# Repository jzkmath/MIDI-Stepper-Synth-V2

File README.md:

# MIDI-Stepper-Synth-V2
This is the Version 2 of my MIDI Stepper Synth. The key differences between this and Version 1 is
that this version uses the Terasic DE0-nano (Cyclone IV) FPGA as the controller instead of Arduino.
The key advantage to doing so is that an FPGA can execute commands at the same time instead of sequentially.
This also allows for a better understanding of how MIDI actually works, because the MIDI has to be decoded manually
instead of using a MIDI library.

This project is being performed at the Virginia Tech AMP Lab, and the project can be seen (Link is dead)

Alternatively, you can view the project documentation/Notes in the "Project Documentation" folder and opening the "Documentation.md" file.

**Please use the project page or PDF to see the BOM and all information on this project!!!**

Since MIDI uses a specific type of UART, the FPGA will take the serial data and convert it to parallel, as a 3 byte register.
Once this is done, the message is decoded such that the stepper motors react accordingly. 

## Basic MIDI Layout
The 3 byte MIDI Message is as Follows:
**1XXXCCCC 0NNNNNNN 0VVVVVVV**
- **X** - MIDI Command. This is 1000 for Note OFF, and 1001 for Note ON.
- **C** - MIDI Channel. 
- **N** - MIDI Note. This is the pitch that is specified. 60 for example is Middle C or C4.
- **V** - MIDI Velocity. This is similar to volume.

The general idea is that we want to turn the MIDI value into a stepper speed. To do this, we use a
similar method to how version 1 handles this, except this time we use clock cycles instead of time.
The DE0-nano has a 50 MHz clock, so we can generate a square wave at a specific frequency by counting
a certain number of clock cycles and toggling the state of a pin. 
The code simply takes the MIDI note value and converts it to the corresponding number of clock cycles
needed to do so.

In addition to the functions of version 1, version 2 also uses the velocity information to control 
how many steppers turn. The higher the velocity, the more stepper motors turn on (ranging from 0-4)
This is how the array of floppy drives work on the popular "Floppotron" on YouTube.

## Block Diagram

## Principle of Operation

The first thing that must be done to convert MIDI into stepper music is that we need to decode the MIDI signal. MIDI uses 31250 baud UART (Universal Asynchronous Recieve Transmit) to send an recieve data. This is a form of serial, so we need to load this into a register to act upon with combinational logic. To do this, we use a Finite State Machine, or FSM with two states; Idle and Read. 
In the Idle state, the Rx line is high. When a device wants to send a message, the Rx line is dropped low. This is known as the start bit and the actual data is the 8 bits that follow, then the line goes high again (called the stop bit).

Knowing this, we can use the start bit as a means to change to the read state. 

In the read state, we want to look at the Rx line in the middle of each bit and shift that bit into our register. To do this, we count a certain number of clock cycles to get to the center of the bit. Given that the DE0-nano has a 50MHz clock and MIDI is 31250 baud, that means that it takes 800 clock cycles to get to the center of a bit, and 1600 clock cycles to go from center to center.

When the start bit is detected the read process is as follows:
1. count 800 clock cycles to get to the center of the start bit
2. count 1600 clock cycles to get to the center of the data bit
3. shift in the value of the Rx line
4. repeat steps 2 and 3 a total of 8 times
5. output the shifted value
6. wait for the Rx line to go high (stop bit detected) and go back to the Idle state.

Once we do that, we have our byte of data. Knowing that MIDI is 3 bytes of data, we take the byte and shift it into a larger, 3 byte register. After that, we can use combinational logic to control the stepper motors.

MIDI has a byte of control information (Command and Channel) and two bytes of data (Pitch and Velocity). We want to use the first byte to properly route the last two bytes appropriately. To do this, we have a single data router module and register modules for each channel. The registers have an enable and clear control signal and will either load or clear their contents depending on which input is pulled high. The second and third bytes are connected to the inputs of all the registers via a common bus and the first byte is used by the router module to control which register gets enable or clear pulled high. Note on (1001) or Note Off (1000) determines whether the register is enabled or cleared, and the channel determines which channel this happens to.

Once the register has the data, we need to convert the pitch into clock cycles. We look at the pitch value and corresponding frequency. We then figure out how many clock cycles elapse in half the period of the note. We do half because we want to create a square wave, which has a 50% duty cycle.

Using the converted value, we have a module count up to that value and then toggle the state of the pin. This is the equivalent to the "Blink without delay" sketch that is used in Arduinos (except for FPGAs).

Finally, we use the velocity value to determine how many stepper motors get that signal, which can be anywhere between 0 and 4.

## Credits
The basic UART decoding Verilog code is based off code provided by Electronoobs, modified to be more stable and work with MIDI.

Special Thanks to Robert Perkel and Bob Lineberry for helping with this project and providing assistance with this.

## Legal
This project is under the GNU GPL3.0 Open Source License. 
You are free to use the code in your project, so long as you credit the creator (Jonathan Kayne).
I want people to be able to use my code, but I don't want people to plagiarize my work!

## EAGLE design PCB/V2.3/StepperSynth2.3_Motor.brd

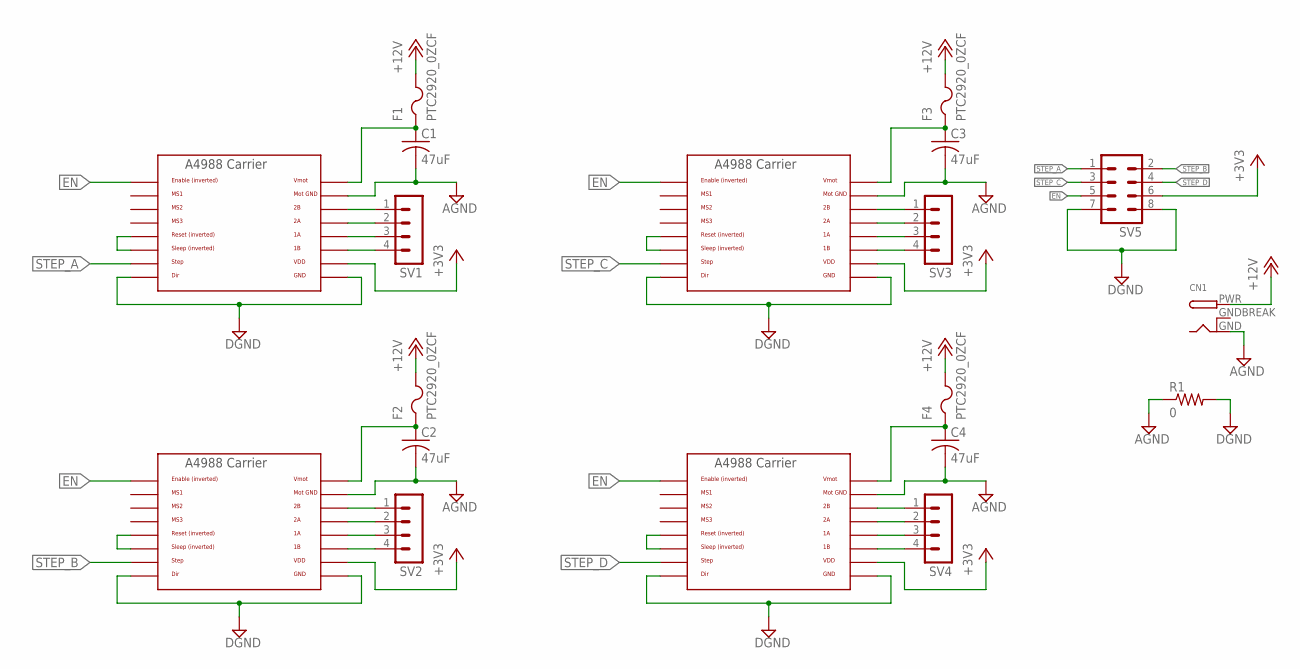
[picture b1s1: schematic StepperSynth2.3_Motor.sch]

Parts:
C1, C2, C3, C4: 47uF; E5-10
CN1: DCBARRELPTH; DCJACK_2MM_PTH
F1, F2, F3, F4: PTC2920_0ZCF; 0ZCF
R1: 0; 0204/5
SV1, SV2, SV3, SV4: MA04-1
SV5: MA04-2
U$1, U$2, U$3, U$4: A4988BREAKOUT

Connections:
+3V3: SV5.6, U$1.VDD, U$2.VDD, U$3.VDD, U$4.VDD
+12V: CN1.PWR, F1.2, F2.2, F3.2, F4.2
AGND: C1.-, C2.-, C3.-, C4.-, CN1.GND, R1.1, U$1.MOTGND, U$2.MOTGND, U$3.MOTGND, U$4.MOTGND
DGND: R1.2, SV5.7, SV5.8, U$1.DIR, U$1.GND, U$2.DIR, U$2.GND, U$3.DIR, U$3.GND, U$4.DIR, U$4.GND
EN: SV5.5, U$1.EN, U$2.EN, U$3.EN, U$4.EN
GNDBREAK: CN1.GNDBREAK
unnamed: SV1.1, U$1.2B
unnamed: SV1.2, U$1.2A
unnamed: SV1.3, U$1.1A
unnamed: SV1.4, U$1.1B
unnamed: U$1.RST, U$1.SLP (SLEEP)
unnamed: C1.+, F1.1, U$1.VMOT
unnamed: SV2.1, U$2.2B
unnamed: SV2.2, U$2.2A
unnamed: SV2.3, U$2.1A
unnamed: SV2.4, U$2.1B
unnamed: U$2.RST, U$2.SLP (SLEEP)
unnamed: C2.+, F2.1, U$2.VMOT
unnamed: SV3.1, U$3.2B
unnamed: SV3.2, U$3.2A
unnamed: SV3.3, U$3.1A
unnamed: SV3.4, U$3.1B
unnamed: U$3.RST, U$3.SLP (SLEEP)
unnamed: C3.+, F3.1, U$3.VMOT
unnamed: SV4.1, U$4.2B
unnamed: SV4.2, U$4.2A
unnamed: SV4.3, U$4.1A
unnamed: SV4.4, U$4.1B
unnamed: U$4.RST, U$4.SLP (SLEEP)
unnamed: C4.+, F4.1, U$4.VMOT
STEP_A: SV5.1, U$1.STEP
STEP_B: SV5.2, U$2.STEP
STEP_C: SV5.3, U$3.STEP
STEP_D: SV5.4, U$4.STEP

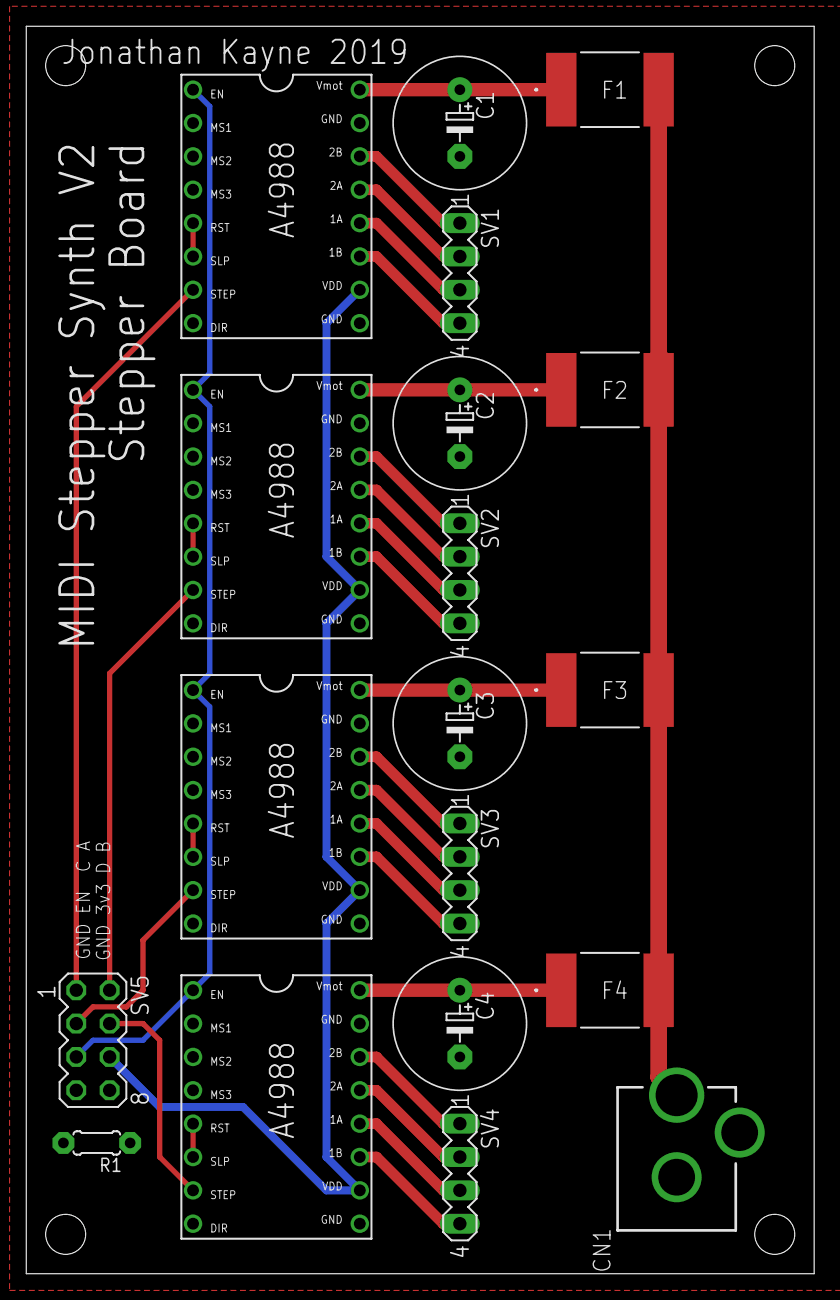
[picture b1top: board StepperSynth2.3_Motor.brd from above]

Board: 2 copper layers, 60.0 x 95.0 mm, 19 parts (0 on the bottom side), 33 nets.

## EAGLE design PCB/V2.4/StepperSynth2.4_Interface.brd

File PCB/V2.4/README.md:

### Stepper Synth V2.4

This is the Final Revision of the MIDI Stepper Synth V2 PCBs. They were designed in Eagle, and rendered in KiCAD.

I added new connectors and changed the header sockets to be in a zigzag pattern so that they would be easier to solder.

## Interface PCB

## Motor PCB

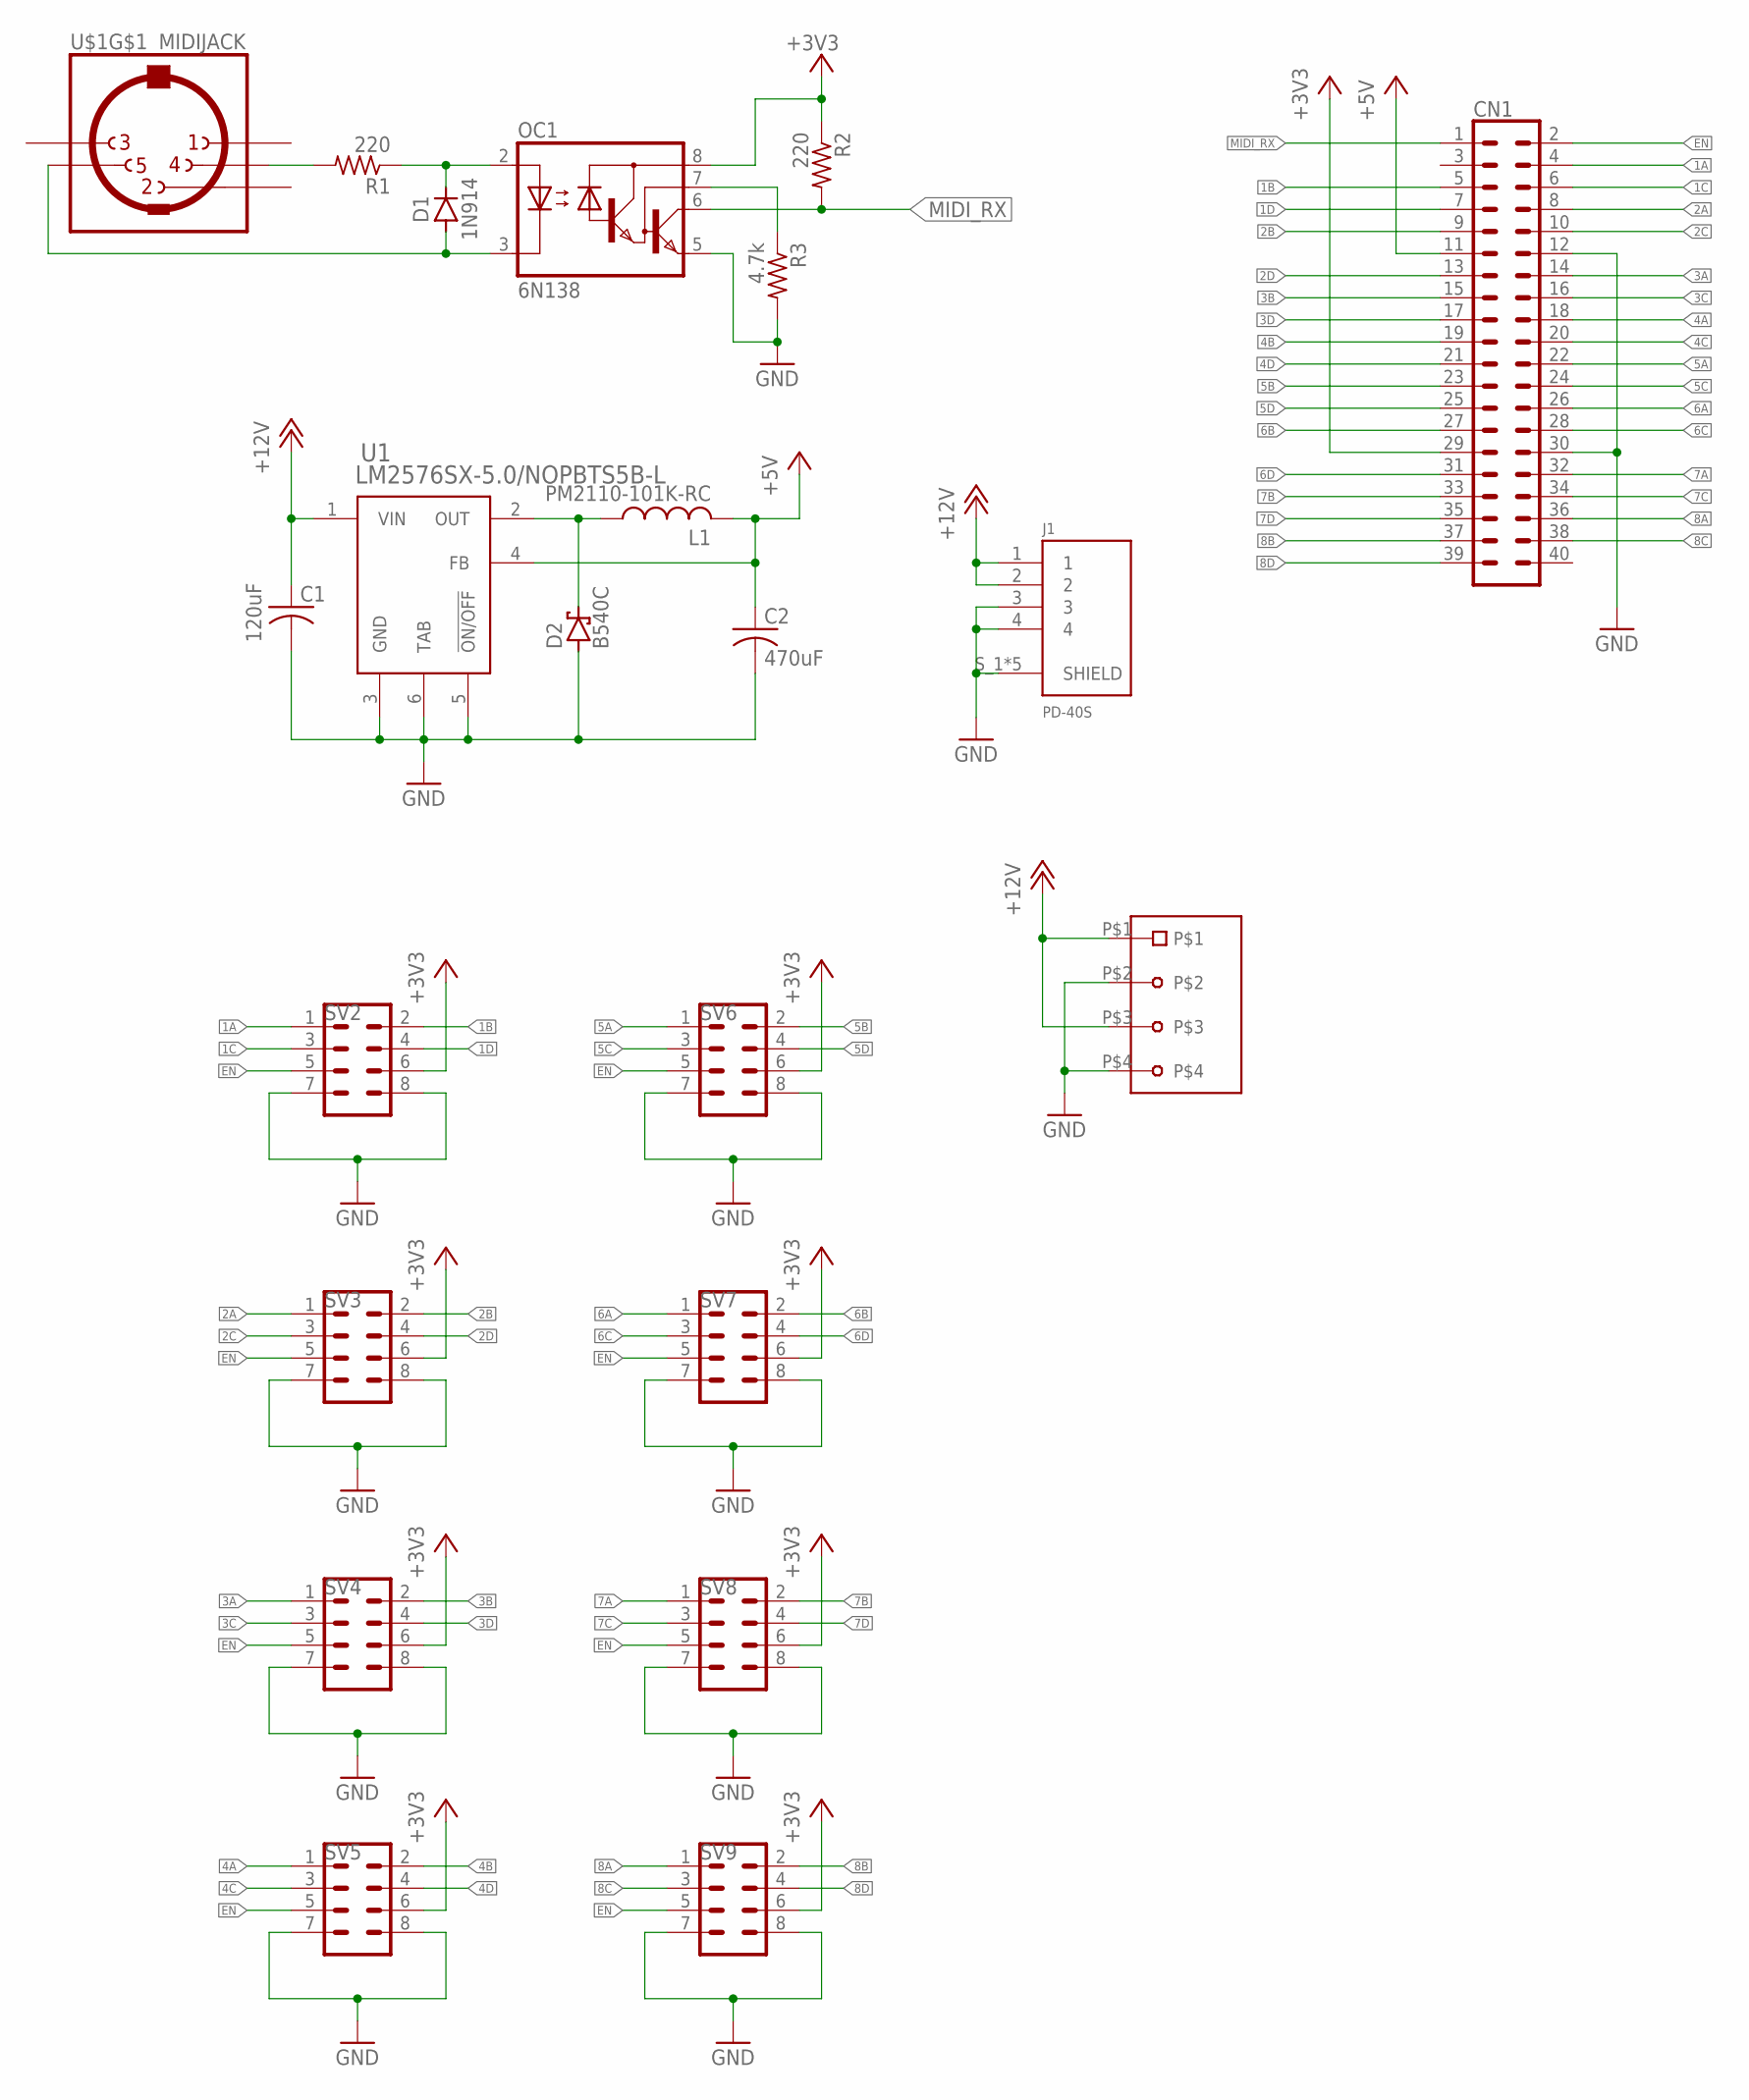
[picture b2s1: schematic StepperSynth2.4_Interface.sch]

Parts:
C1: 120uF; PCAP_SVP_C6-L
C2: 470uF; U2-P-L
CN1: CONN_20X2_LOCK; 1X20_LOCK
CN2: SCREW_TERMINAL_4POS_5MM; 4_POS-SCREW_TERM
D1: 1N914; DO35-7
D2: B540C; SMC
J1: PD-40S; CUI_PD-40S
L1: PM2110-101K-RC; IND_PM2110
OC1: 6N138; DIL08
R1, R2: 220; 0204/7
R3: 4.7k; 0204/7
SV2, SV3, SV4, SV5, SV6, SV7, SV8, SV9: CONN_4X2_LOCK; 1X04_LOCK
U1: LM2576SX-5.0/NOPBTS5B-L; TS5B-L
U$1: MIDIJACK; CP-2350

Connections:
1A: CN1.4, SV2.1
1B: CN1.5, SV2.2
1C: CN1.6, SV2.3
1D: CN1.7, SV2.4
2A: CN1.8, SV3.1
2B: CN1.9, SV3.2
2C: CN1.10, SV3.3
2D: CN1.13, SV3.4
3A: CN1.14, SV4.1
3B: CN1.15, SV4.2
3C: CN1.16, SV4.3
3D: CN1.17, SV4.4
4A: CN1.18, SV5.1
4B: CN1.19, SV5.2
4C: CN1.20, SV5.3
4D: CN1.21, SV5.4
5A: CN1.22, SV6.1
5B: CN1.23, SV6.2
5C: CN1.24, SV6.3
5D: CN1.25, SV6.4
6A: CN1.26, SV7.1
6B: CN1.27, SV7.2
6C: CN1.28, SV7.3
6D: CN1.31, SV7.4
7A: CN1.32, SV8.1
7B: CN1.33, SV8.2
7C: CN1.34, SV8.3
7D: CN1.35, SV8.4
8A: CN1.36, SV9.1
8B: CN1.37, SV9.2
8C: CN1.38, SV9.3
8D: CN1.39, SV9.4
+3V3: CN1.29, OC1.8 (VCC), R2.1, SV2.6, SV3.6, SV4.6, SV5.6, SV6.6, SV7.6, SV8.6, SV9.6
+5V: C2.1 (+), CN1.11, L1.2, U1.4 (FB)
+12V: C1.1 (+), CN2.P$1, CN2.P$3, J1.1, J1.2, U1.1 (VIN)
EN: CN1.2, SV2.5, SV3.5, SV4.5, SV5.5, SV6.5, SV7.5, SV8.5, SV9.5
GND: C1.2 (-), C2.2 (-), CN1.12, CN1.30, CN2.P$2, CN2.P$4, D2.A, J1.3, J1.4, J1.S_1 (SHIELD), J1.S_2 (SHIELD), J1.S_3 (SHIELD), J1.S_4 (SHIELD), J1.S_5 (SHIELD), OC1.5 (GND), R3.2, SV2.7, SV2.8, SV3.7, SV3.8, SV4.7, SV4.8, SV5.7, SV5.8, SV6.7, SV6.8, SV7.7, SV7.8, SV8.7, SV8.8, SV9.7, SV9.8, U1.3 (GND), U1.5 (!ON/OFF), U1.6 (TAB)
MIDI_RX: CN1.1, OC1.6 (VO), R2.2
unnamed: R1.2, U$1.4
unnamed: D1.C, OC1.2 (A), R1.1
unnamed: D1.A, OC1.3 (C), U$1.5
unnamed: OC1.7 (VB), R3.1
unnamed: D2.C, L1.1, U1.2 (OUT)

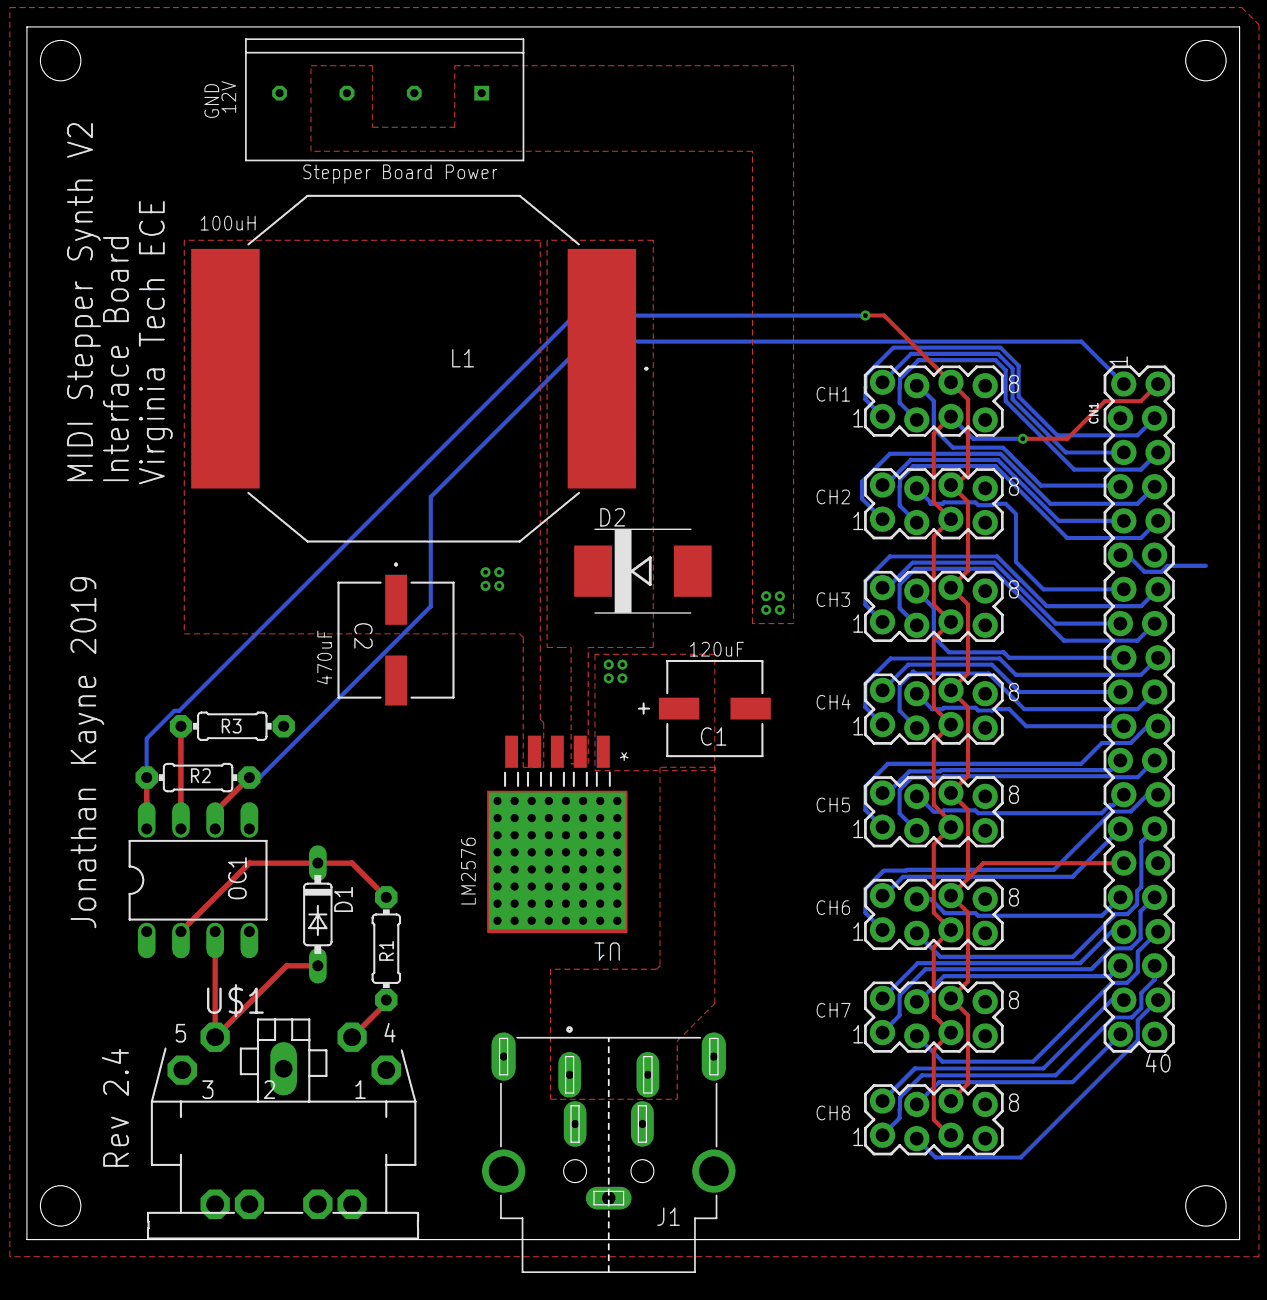
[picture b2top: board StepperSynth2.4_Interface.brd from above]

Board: 2 copper layers, 89.9 x 92.4 mm, 22 parts (0 on the bottom side), 43 nets.

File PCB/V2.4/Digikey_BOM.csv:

"Manufacturer Part Number","Manufacturer","Digi-Key Part Number","Customer Reference","Reference Designator","Packaging","Part Status","Quantity","Unit Price","Extended Price","Quantity Available","Mfg Std Lead Time","Description","RoHS Status","Lead Free Status","REACH Status","US Tariff Status"
"VES120PS12","XP Power","1470-3639-ND","","","Box","Active","1","62.00000","$62.00","498","21 Weeks","EXTERNAL PSU, 120W, LEVEL VI","RoHS Compliant","Lead free","Not Available","Tariff Eligible"
"PD-40S","CUI Inc.","CP-7240-ND","","","Tray","Active","1","2.59000","$2.59","12445","14 Weeks","CONN JACK FMALE DIN 4POS SOLDER","RoHS Compliant","Lead free","Not Available","Tariff Eligible"
"OSTTA020161","On Shore Technology Inc.","ED2561-ND","","","Bulk","Active","8","0.69000","$5.52","16887","12 Weeks","TERM BLK 2POS SIDE ENTRY 5MM PCB","RoHS Compliant","Lead free","REACH Unaffected","Tariff Applied"
"OSTTA040161","On Shore Technology Inc.","ED2563-ND","","","Bulk","Active","1","1.05000","$1.05","976","12 Weeks","TERM BLK 4POS SIDE ENTRY 5MM PCB","RoHS Compliant","Lead free","REACH Unaffected","Tariff Applied"
"61300411121","Wurth Electronics Inc.","732-5317-ND","","","Bag","Active","32","0.12720","$4.07","16252","14 Weeks","CONN HEADER VERT 4POS 2.54MM","RoHS Compliant","Lead free","REACH Unaffected",""
"PPTC081LFBN-RC","Sullins Connector Solutions","S7006-ND","","","Tray","Active","64","0.60800","$38.91","21240","5 Weeks","CONN HDR 8POS 0.1 TIN PCB","RoHS Compliant","Lead free","REACH Unaffected",""
"0ZCF0100AF2A","Bel Fuse Inc.","507-2070-1-ND","","","Cut Tape (CT)","Active","32","0.49100","$15.71","9184","18 Weeks","PTC RESET FUSE 60V 1A 2920","RoHS Compliant","Lead free","REACH Unaffected",""
"UHE2A470MPD1TD","Nichicon","493-14555-1-ND","","","Cut Tape (CT)","Active","36","0.36000","$12.96","50826","16 Weeks","CAP ALUM 47UF 20% 100V RADIAL","RoHS Compliant","Lead free","REACH Unaffected",""
"M20-9760442","Harwin Inc.","952-3276-ND","","","Bulk","Active","16","0.31900","$5.10","3637","10 Weeks","CONN HEADER VERT 8POS 2.54MM","RoHS Compliant","Lead free","REACH Unaffected",""
"SDS-50J","CUI Inc.","CP-2350-ND","","","Tray","Active","1","1.96000","$1.96","24579","14 Weeks","CONN RCPT FMALE DIN 5POS SOLDER","RoHS Compliant","Lead free","Not Available","Tariff Applied"
"A 08-LC-TT","Assmann WSW Components","AE9986-ND","","","Tube","Active","1","0.18000","$0.18","100334","20 Weeks","CONN IC DIP SOCKET 8POS TIN","RoHS Compliant","Lead free","REACH Unaffected","Tariff Eligible"
"1N914","ON Semiconductor","1N914FS-ND","","","Bulk","Active","1","0.10000","$0.10","50588","17 Weeks","DIODE GEN PURP 100V 200MA DO35","RoHS Compliant","Lead free","REACH Unaffected","Tariff Applied"
"61304021121","Wurth Electronics Inc.","732-5310-ND","","","Bag","Active","1","1.89000","$1.89","924","14 Weeks","CONN HEADER VERT 40POS 2.54MM","RoHS Compliant","Lead free","REACH Unaffected",""
"20SVPF120M","Panasonic Electronic Components","P16498CT-ND","","","Cut Tape (CT)","Active","1","1.29000","$1.29","34887","9 Weeks","CAP ALUM POLY 120UF 20% 20V SMD","RoHS Compliant","Lead free","Not Available",""
"UUD1A471MNL1GS","Nichicon","493-2252-1-ND","","","Cut Tape (CT)","Active","1","0.68000","$0.68","34069","18 Weeks","CAP ALUM 470UF 20% 10V SMD","RoHS Compliant","Lead free","REACH Unaffected",""
"B540C-13-F","Diodes Incorporated","B540C-FDICT-ND","","","Cut Tape (CT)","Active","1","0.50000","$0.50","259459","13 Weeks","DIODE SCHOTTKY 40V 5A SMC","RoHS Compliant","Contains lead","REACH Unaffected",""
"PM2110-101K-RC","Bourns Inc.","M8767-ND","","","Bulk","Active","1","2.96000","$2.96","2757","20 Weeks","FIXED IND 100UH 5.4A 32 MOHM SMD","RoHS Compliant","Lead free","REACH Unaffected",""
"LM2576SX-5.0/NOPB","Texas Instruments","LM2576SX-5.0/NOPBCT-ND","","","Cut Tape (CT)","Active","1","2.86000","$2.86","41842","16 Weeks","IC REG BUCK 5V 3A TO263-5","RoHS Compliant","Contains lead","REACH Unaffected",""
"1988","Adafruit Industries LLC","1528-2235-ND","","","Bulk","Active","1","2.95000","$2.95","348","12 Weeks","GPIO RIBBON CABLE FOR RASPBERRY","Not Available","Not Available","Not Available","Tariff Eligible"
"71600-008LF","Amphenol ICC (FCI)","609-3568-ND","","","Tube","Active","16","0.87000","$13.92","6728","8 Weeks","CONN RCPT 8POS IDC 28-30AWG GOLD","RoHS Compliant","Lead free","Not Available",""
"28L0138-50R-10","Laird-Signal Integrity Products","240-2512-1-ND","","","Cut Tape (CT)","Active","10","0.07700","$0.77","44108","8 Weeks","FERRITE BEAD 153 OHM AXIAL 1LN","RoHS Compliant","Lead free","REACH Unaffected","Tariff Applied"
"CFM14JT220R","Stackpole Electronics Inc","S220QCT-ND","","","Cut Tape (CT)","Active","2","0.10000","$0.20","37986","15 Weeks","RES 220 OHM 1/4W 5% CF MINI","RoHS Compliant","Lead free","REACH Unaffected","Tariff Applied"
"CFM14JT4K70","Stackpole Electronics Inc","S4.7KQCT-ND","","","Cut Tape (CT)","Active","1","0.10000","$0.10","65820","15 Weeks","RES 4.7K OHM 1/4W 5% CF MINI","RoHS Compliant","Lead free","REACH Unaffected","Tariff Applied"
"3801/04","3M","3M156838-10-ND","","","Bulk","Active","1","3.79000","$3.79","9","Not Available","CBL RIBN 4COND 0.050 GRAY 10'","RoHS Compliant","Lead free","Not Available",""
"6N138","Lite-On Inc.","160-1795-ND","","","Tube","Active","1","0.81000","$0.81","4836","10 Weeks","OPTOISO 5KV DARL W/BASE 8DIP","RoHS Compliant","Lead free","Not Available",""

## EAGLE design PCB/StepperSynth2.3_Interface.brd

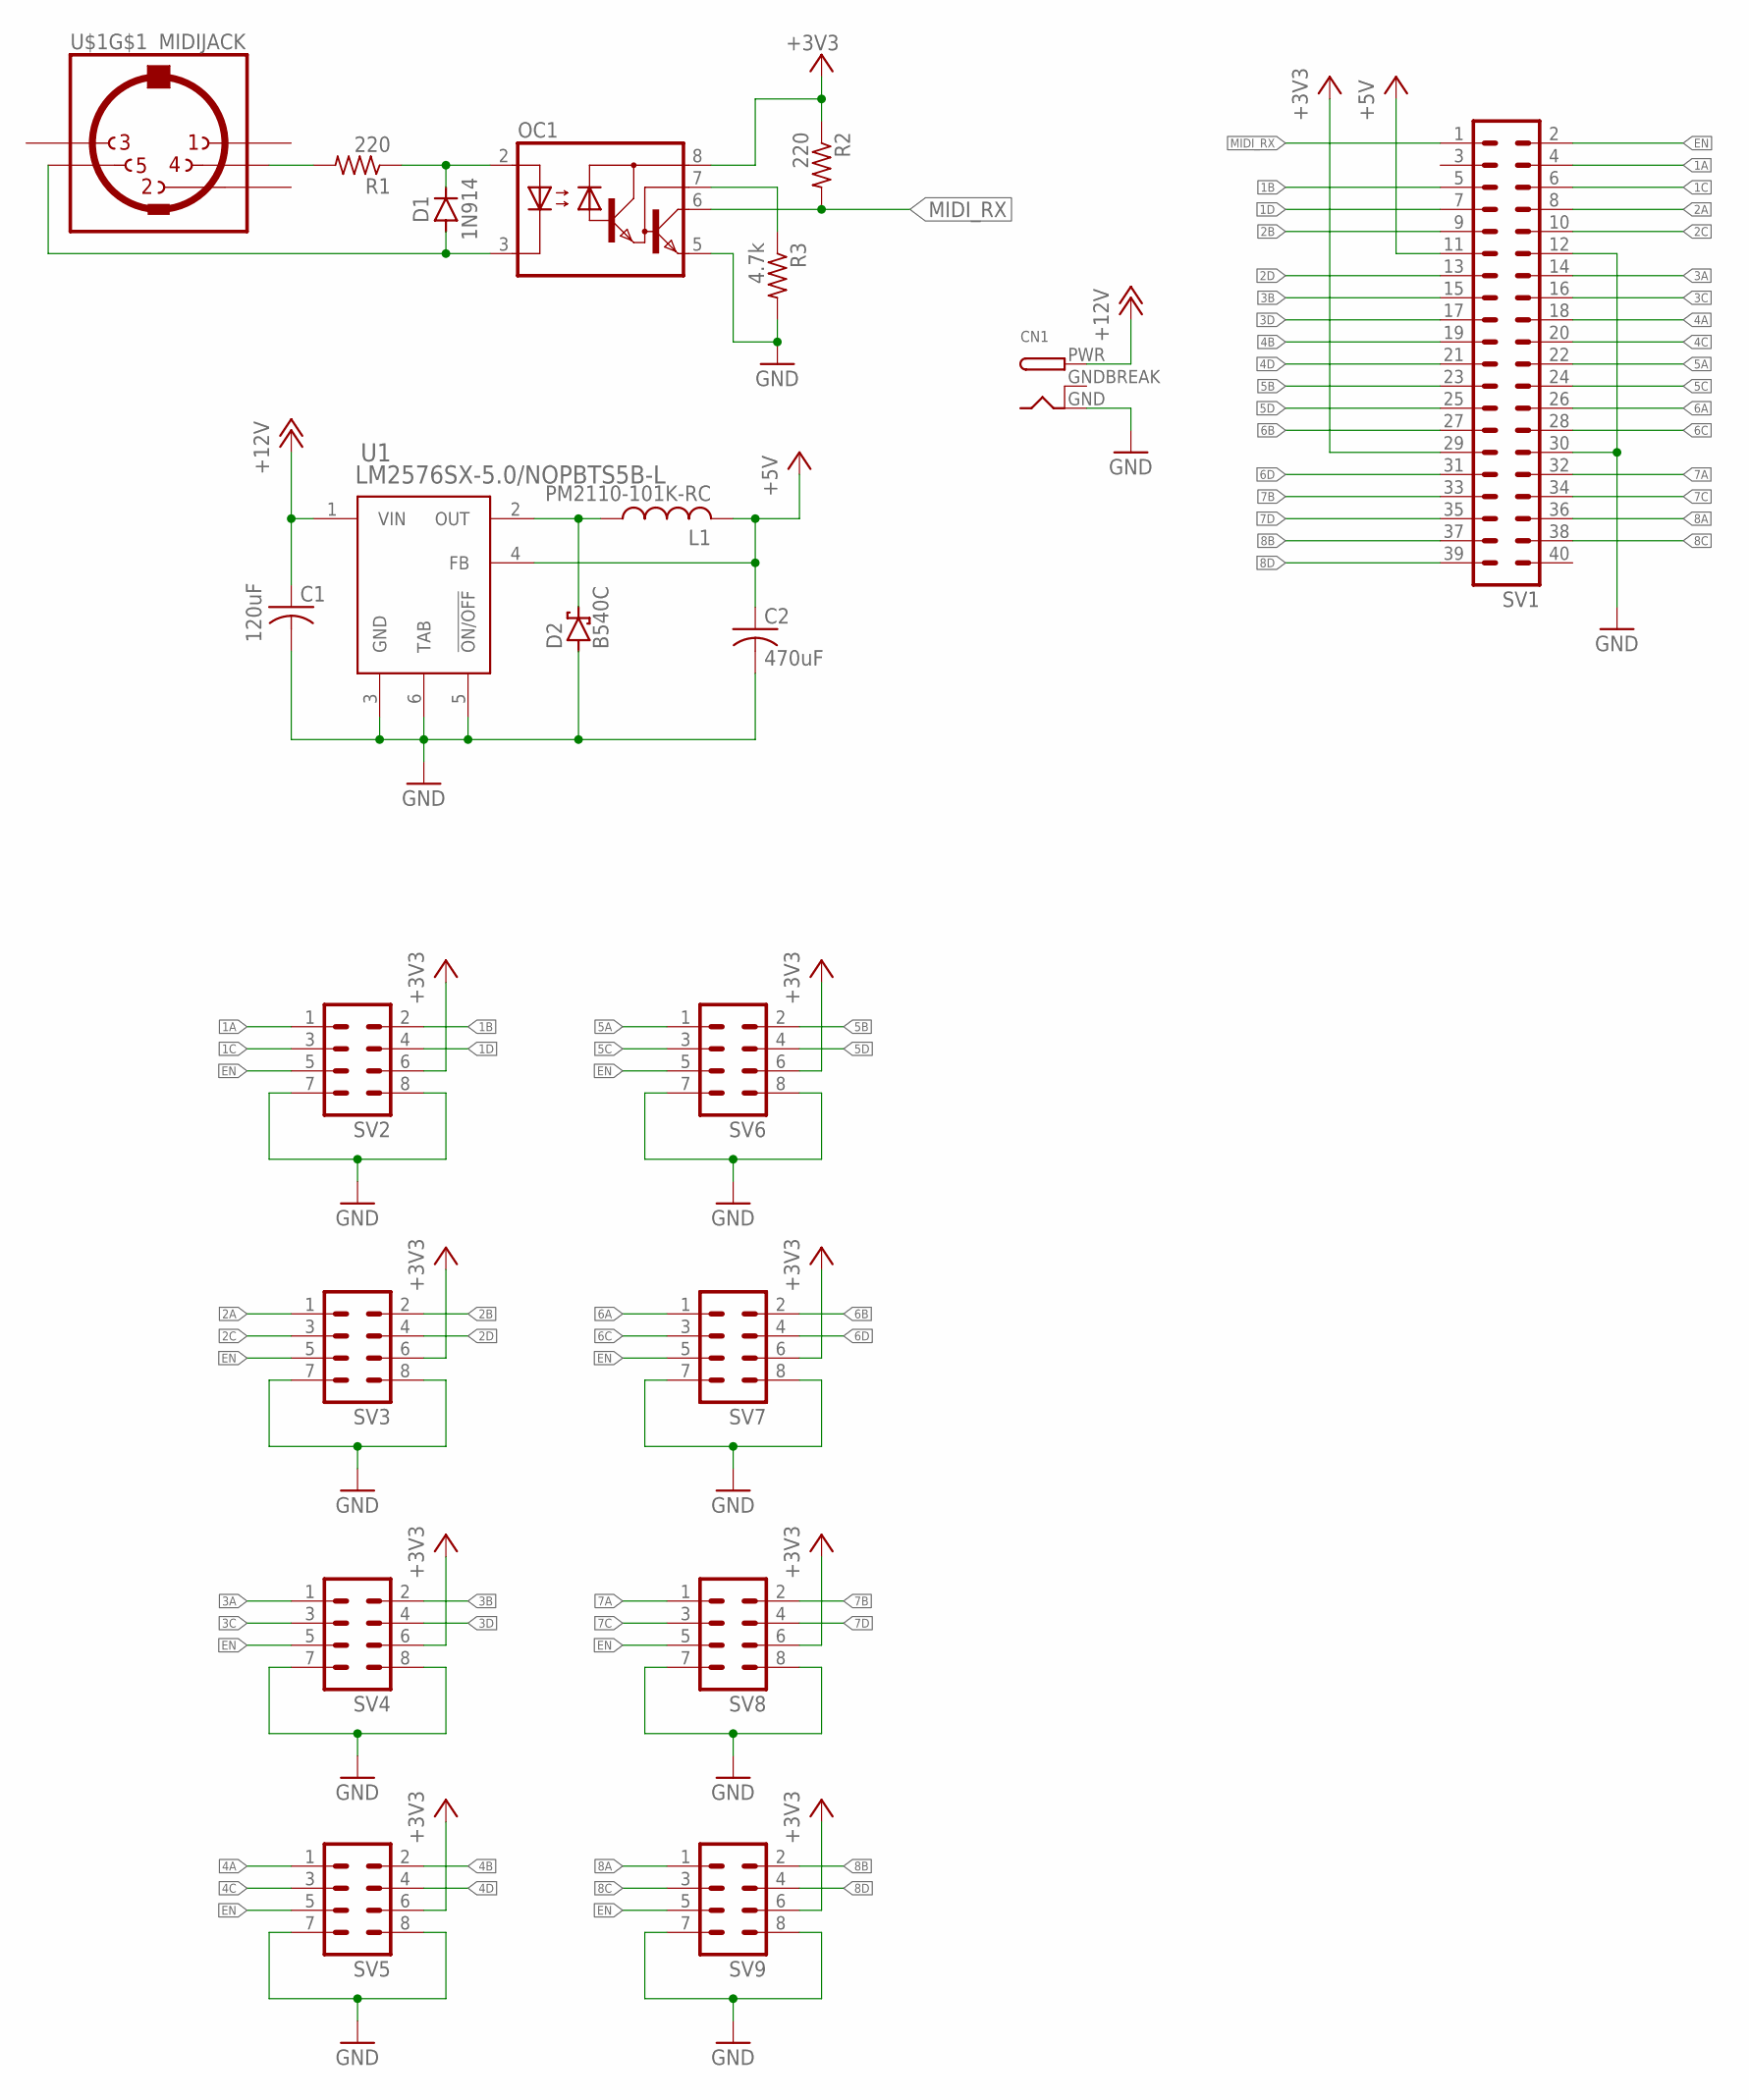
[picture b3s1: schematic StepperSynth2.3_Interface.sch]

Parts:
C1: 120uF; PCAP_SVP_C6-L
C2: 470uF; U2-P-L
CN1: DCBARRELPTH; DCJACK_2MM_PTH
D1: 1N914; DO35-7
D2: B540C; SMC
L1: PM2110-101K-RC; IND_PM2110
OC1: 6N138; DIL08
R1, R2: 220; 0204/5
R3: 4.7k; 0204/5
SV1: MA20-2
SV2, SV3, SV4, SV5, SV6, SV7, SV8, SV9: MA04-2
U1: LM2576SX-5.0/NOPBTS5B-L; TS5B-L
U$1: MIDIJACK; CP-2350

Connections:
1A: SV1.4, SV2.1
1B: SV1.5, SV2.2
1C: SV1.6, SV2.3
1D: SV1.7, SV2.4
2A: SV1.8, SV3.1
2B: SV1.9, SV3.2
2C: SV1.10, SV3.3
2D: SV1.13, SV3.4
3A: SV1.14, SV4.1
3B: SV1.15, SV4.2
3C: SV1.16, SV4.3
3D: SV1.17, SV4.4
4A: SV1.18, SV5.1
4B: SV1.19, SV5.2
4C: SV1.20, SV5.3
4D: SV1.21, SV5.4
5A: SV1.22, SV6.1
5B: SV1.23, SV6.2
5C: SV1.24, SV6.3
5D: SV1.25, SV6.4
6A: SV1.26, SV7.1
6B: SV1.27, SV7.2
6C: SV1.28, SV7.3
6D: SV1.31, SV7.4
7A: SV1.32, SV8.1
7B: SV1.33, SV8.2
7C: SV1.34, SV8.3
7D: SV1.35, SV8.4
8A: SV1.36, SV9.1
8B: SV1.37, SV9.2
8C: SV1.38, SV9.3
8D: SV1.39, SV9.4
+3V3: OC1.8 (VCC), R2.1, SV1.29, SV2.6, SV3.6, SV4.6, SV5.6, SV6.6, SV7.6, SV8.6, SV9.6
+5V: C2.1 (+), L1.2, SV1.11, U1.4 (FB)
+12V: C1.1 (+), CN1.PWR, U1.1 (VIN)
EN: SV1.2, SV2.5, SV3.5, SV4.5, SV5.5, SV6.5, SV7.5, SV8.5, SV9.5
GND: C1.2 (-), C2.2 (-), CN1.GND, D2.A, OC1.5 (GND), R3.2, SV1.12, SV1.30, SV2.7, SV2.8, SV3.7, SV3.8, SV4.7, SV4.8, SV5.7, SV5.8, SV6.7, SV6.8, SV7.7, SV7.8, SV8.7, SV8.8, SV9.7, SV9.8, U1.3 (GND), U1.5 (!ON/OFF), U1.6 (TAB)
GNDBREAK: CN1.GNDBREAK
MIDI_RX: OC1.6 (VO), R2.2, SV1.1
unnamed: R1.2, U$1.4
unnamed: D1.C, OC1.2 (A), R1.1
unnamed: D1.A, OC1.3 (C), U$1.5
unnamed: OC1.7 (VB), R3.1
unnamed: D2.C, L1.1, U1.2 (OUT)

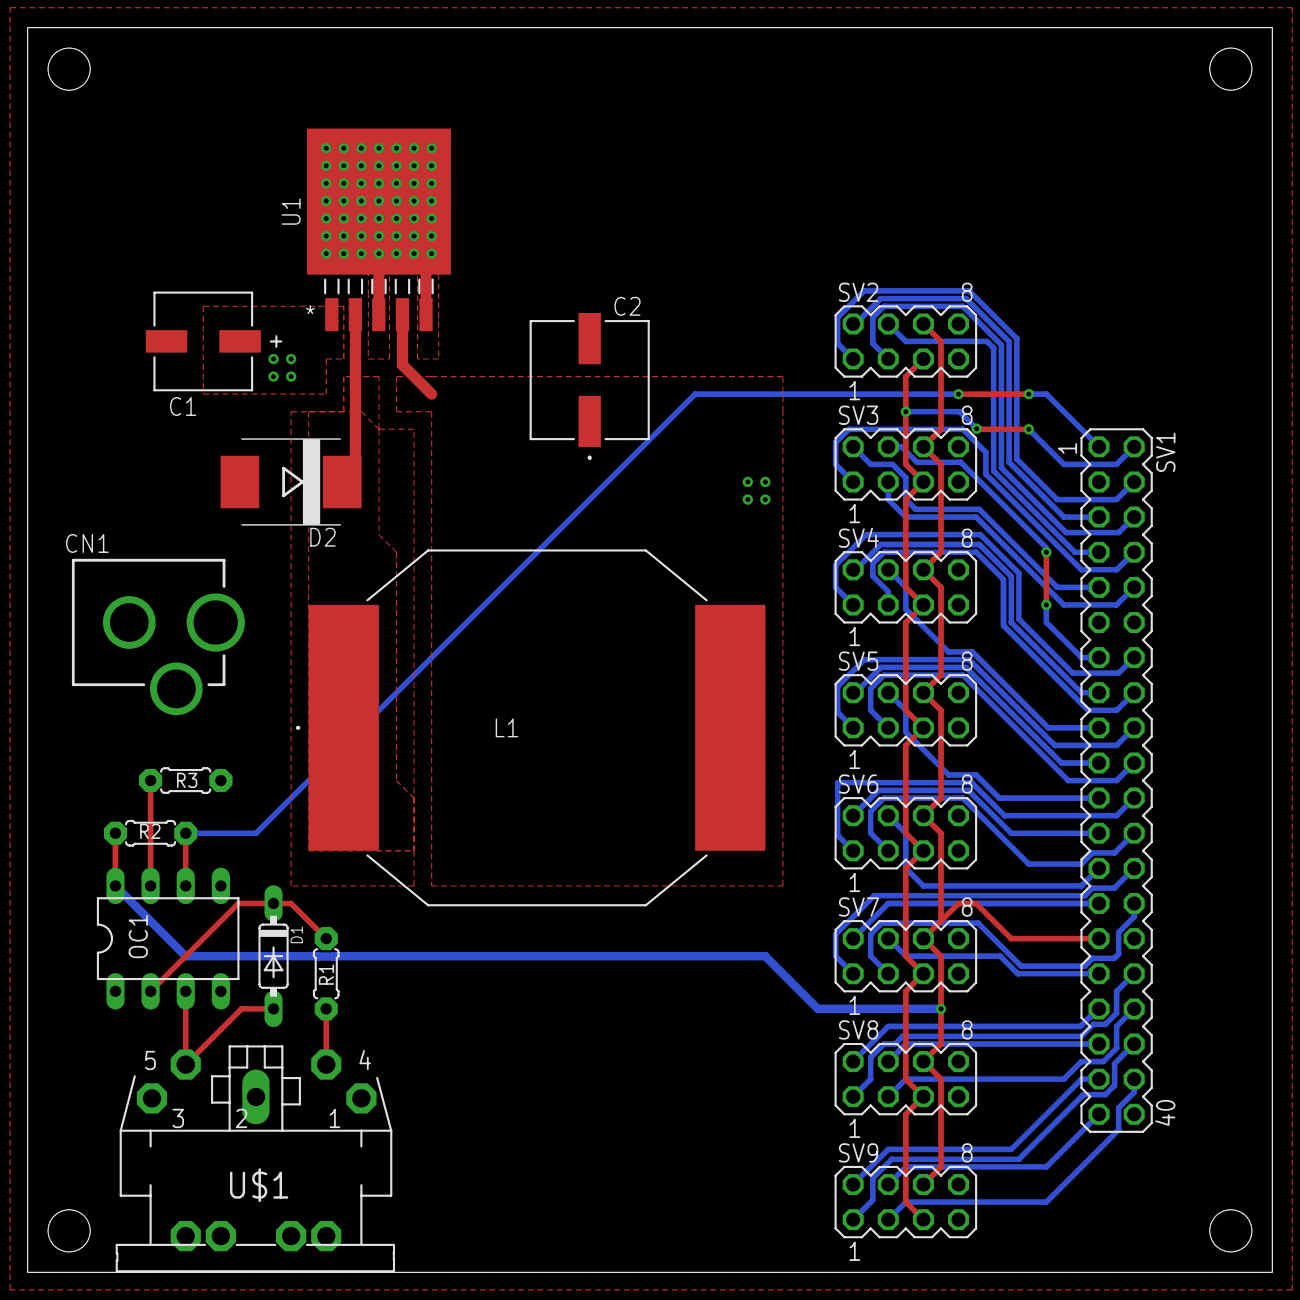
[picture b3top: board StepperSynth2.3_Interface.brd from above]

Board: 2 copper layers, 90.0 x 90.0 mm, 21 parts (0 on the bottom side), 43 nets.

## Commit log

2019-01-07 Create jkjk
2019-01-07 Create jlkl
2019-01-07 First iteration of the verilog code
2019-01-16 Create klk
2019-02-02 Updated LED Switch control
2019-02-09 Rename SoidWorks/jkjk to SolidWorks/jj
2019-02-09 Renamed to SolidWorks
2019-02-11 Update README.md
    Added the Principle of operation
2019-02-20 Replaced the MIDI files
2019-02-20 Updated MIDI channels
    MIDI channels are now on channels 1-8
2019-02-24 Added V2.4
2019-03-07 added more MIDI Files
2019-04-19 Added BOM Spreadsheet
    Includes a CSV for direct upload to Digikey
2019-04-23 Fixed BOM
2019-05-17 More MIDI
2021-02-08 2021 update
    added all my songs
2021-03-11 Fixed images
2024-12-05 moved images
2024-12-05 updating documentation file 1
2024-12-05 update documentation 2
